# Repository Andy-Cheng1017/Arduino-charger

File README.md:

# Arduino-charger
 Atmega328pau+TypeC+li-on Charger boost PCB

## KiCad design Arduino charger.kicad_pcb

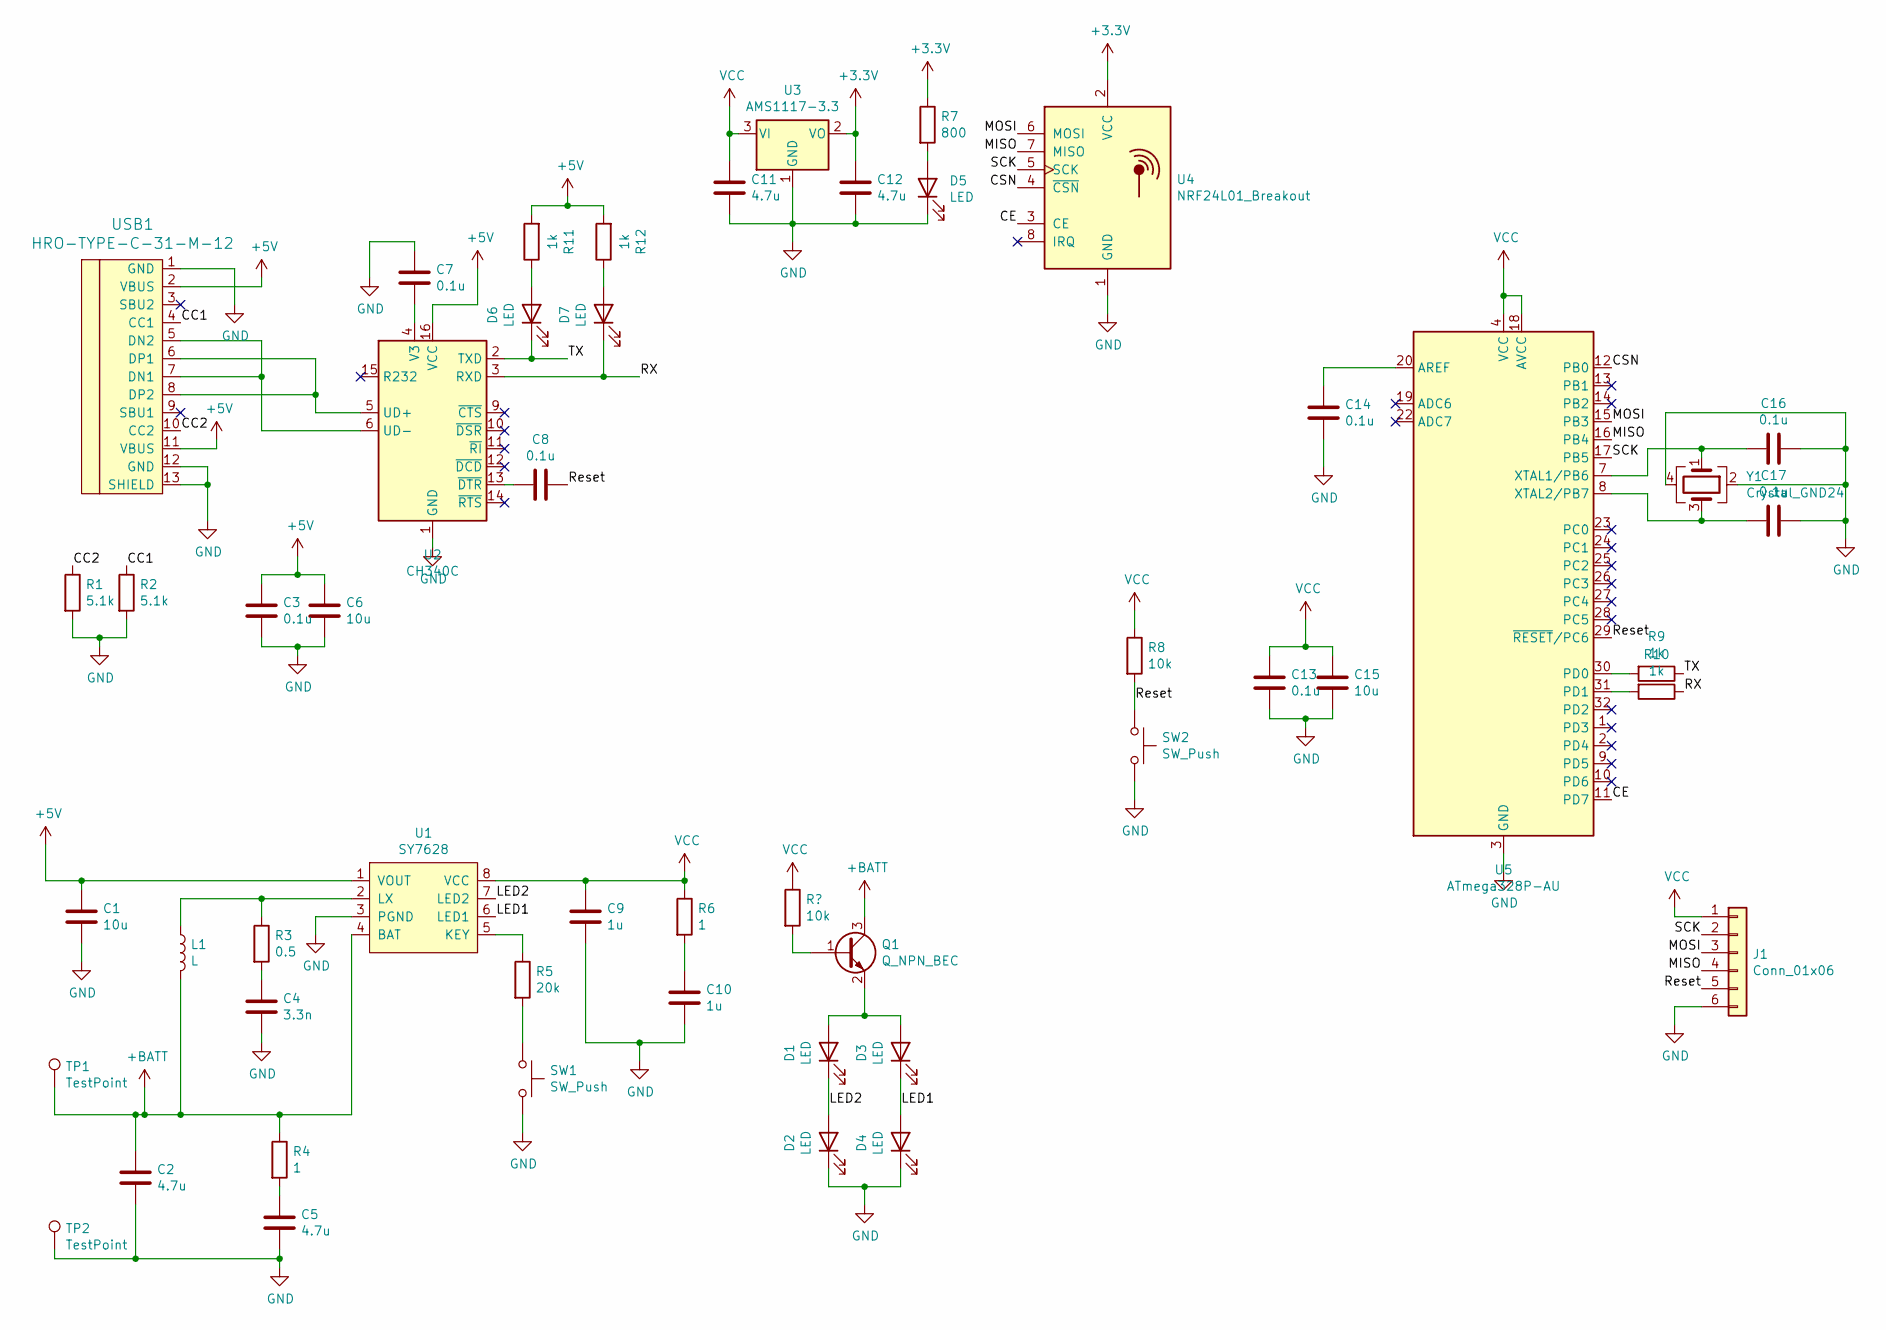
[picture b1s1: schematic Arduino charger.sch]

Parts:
C1, C6, C15: 10u; C_1206_3216Metric
C2, C5, C11, C12: 4.7u; C_0805_2012Metric
C3, C7, C8, C13, C14, C16, C17: 0.1u; C_0805_2012Metric
C4: 3.3n; C_0805_2012Metric
C9, C10: 1u; C_0805_2012Metric
D1, D2, D3, D4, D5, D6, D7: LED; LED_0805_2012Metric
J1: Conn_01x06; PinHeader_1x06_P2.54mm_Vertical
L1: L; L_Bourns-SRN4018
Q1: Q_NPN_BEC; SOT-23
R1, R2: 5.1k; R_0805_2012Metric
R3: 0.5; R_0805_2012Metric
R4, R6: 1; R_0805_2012Metric
R5: 20k; R_0805_2012Metric
R7: 800; R_0805_2012Metric
R8: 10k; R_0805_2012Metric
R9, R10, R11, R12: 1k; R_0805_2012Metric
SW1, SW2: SW_Push; SW_SPST_CK_RS282G05A3
TP1, TP2: TestPoint; TestPoint_Pad_D2.5mm
U1: SY7628; SOIC-8_3.9x4.9mm_P1.27mm
U2: CH340C; SOIC-16_3.9x9.9mm_P1.27mm
U3: AMS1117-3.3; SOT-223-3_TabPin2
U4: NRF24L01_Breakout; NRF24L01-SMD
U5: ATmega328P-AU; TQFP-32_7x7mm_P0.8mm
USB1: HRO-TYPE-C-31-M-12
Y1: Crystal_GND24; Crystal_SMD_3225-4Pin_3.2x2.5mm

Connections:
+3V3: C12.2, R7.1, U3.2 (VO), U4.2 (VCC)
+5V: C1.1, C3.1, C6.1, R11.2, R12.2, U1.1 (VOUT), U2.16 (VCC), USB1.2 (VBUS), USB1.11 (VBUS)
+BATT: C2.2, L1.2, Q1.3 (C), R4.1, TP1.1, U1.4 (BAT)
/CC1: R2.1, USB1.4 (CC1)
/CC2: R1.1, USB1.10 (CC2)
/CE: U4.3 (CE), U5.11 (PD7)
/CSN: U4.4 (~CSN), U5.12 (PB0)
/LED1: D3.1 (K), D4.2 (A), U1.6 (LED1)
/LED2: D1.1 (K), D2.2 (A), U1.7 (LED2)
/MISO: J1.4, U4.7 (MISO), U5.16 (PB4)
/MOSI: J1.3, U4.6 (MOSI), U5.15 (PB3)
/RX: D7.1 (K), R10.1, U2.3 (RXD)
/Reset: C8.1, J1.5, R8.2, SW2.1, U5.29 (~RESET~/PC6)
/SCK: J1.2, U4.5 (SCK), U5.17 (PB5)
/TX: D6.1 (K), R9.1, U2.2 (TXD)
GND: C1.2, C2.1, C3.2, C4.1, C5.1, C6.2, C7.1, C9.1, C10.1, C11.1, C12.1, C13.2, C14.1, C15.2, C16.2, C17.2, D2.1 (K), D4.1 (K), D5.1 (K), J1.6, R1.2, R2.2, SW1.2, SW2.2, TP2.1, U1.3 (PGND), U2.1 (GND), U3.1 (GND), U4.1 (GND), U5.3 (GND), U5.5 (GND), U5.21 (GND), USB1.1 (GND), USB1.12 (GND), USB1.13 (SHIELD), Y1.2, Y1.4
unnamed: C4.2, R3.2
unnamed: C5.2, R4.2
unnamed: C7.2, U2.4 (V3)
unnamed: C8.2, U2.13 (~DTR)
unnamed: C10.2, R6.2
unnamed: C14.2, U5.20 (AREF)
unnamed: C16.1, U5.7 (XTAL1/PB6), Y1.1
unnamed: C17.1, U5.8 (XTAL2/PB7), Y1.3
unnamed: D1.2 (A), D3.2 (A), Q1.2 (E)
unnamed: D5.2 (A), R7.2
unnamed: D6.2 (A), R11.1
unnamed: D7.2 (A), R12.1
unnamed: L1.1, R3.1, U1.2 (LX)
unnamed 29: Q1.1 (B); also elsewhere on the board
unnamed: R5.1, U1.5 (KEY)
unnamed: R5.2, SW1.1
unnamed: R9.2, U5.30 (PD0)
unnamed: R10.2, U5.31 (PD1)
unnamed: U2.5 (UD+), USB1.6 (DP1), USB1.8 (DP2)
unnamed: U2.6 (UD-), USB1.5 (DN2), USB1.7 (DN1)
VCC: C9.2, C11.2, C13.1, C15.1, J1.1, R6.1, R8.1, U1.8 (VCC), U3.3 (VI), U5.4 (VCC), U5.6 (VCC), U5.18 (AVCC); also elsewhere on the board

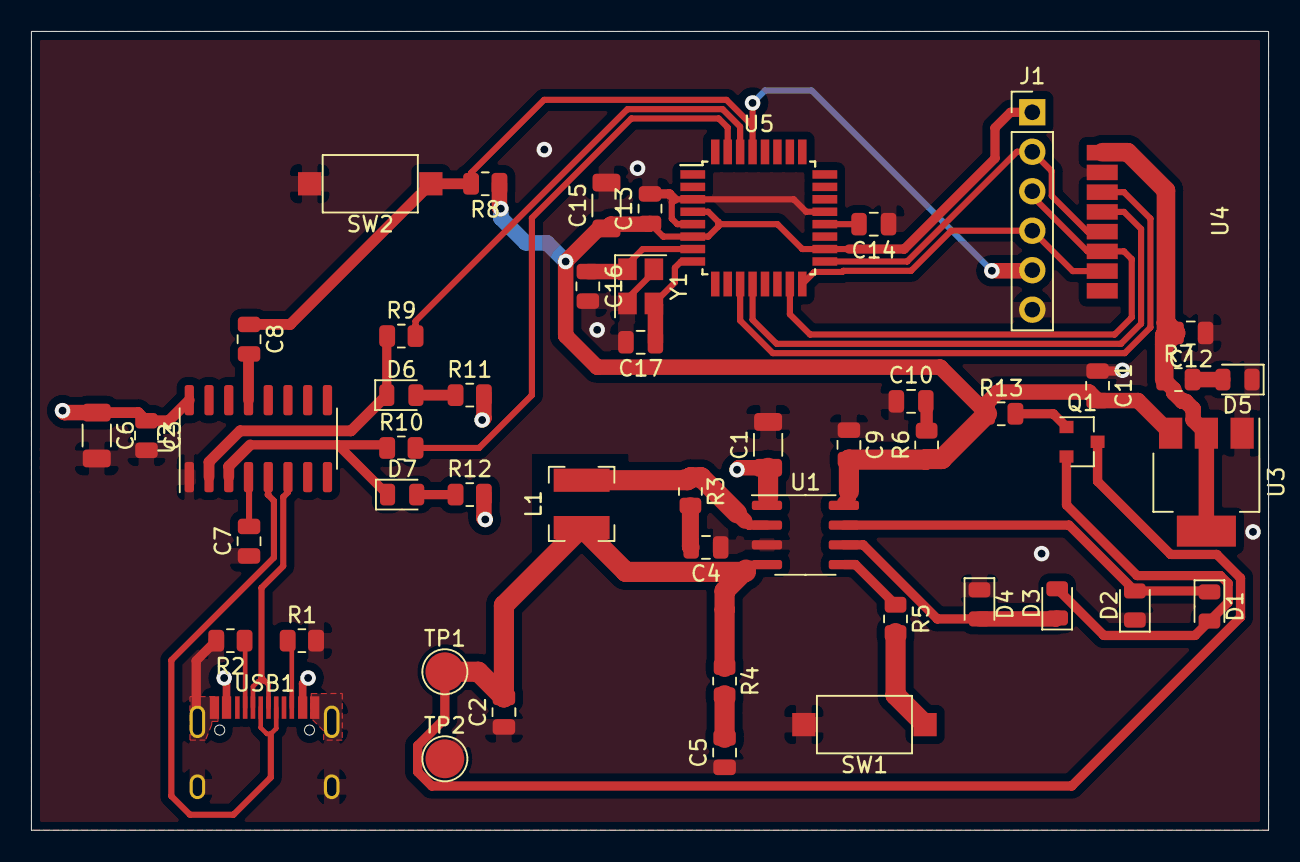
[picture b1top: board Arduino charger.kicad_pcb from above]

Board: 2 copper layers, 79.6 x 51.4 mm, 51 parts (0 on the bottom side), 37 nets.

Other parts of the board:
R13: 10k; R_0805_2012Metric

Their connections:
unnamed 29: R13.2; also elsewhere on the board
VCC: R13.1; also elsewhere on the board

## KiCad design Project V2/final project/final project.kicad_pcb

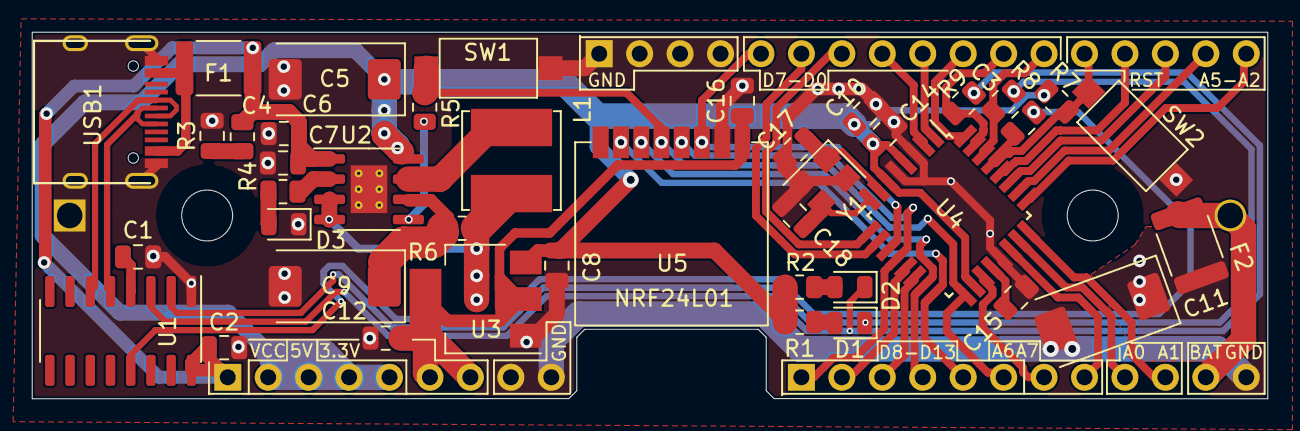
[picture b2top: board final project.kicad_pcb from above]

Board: 2 copper layers, 77.6 x 23.0 mm, 45 parts (1 on the bottom side), 47 nets.

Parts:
BT1: Battery_Cell; BatteryHolder_MPD_BH-18650-PC2
C1, C3, C14, C15, C16: 0.1u; C_0805_2012Metric
C2, C8, C12: 1u; C_0805_2012Metric
C4, C6, C7, C10: 4.7u; C_0805_2012Metric
C5: 150u; CP_EIA-7343-15_Kemet-W
C9, C11: 22u; CP_EIA-7343-15_Kemet-W
C17, C18: 22p; C_0805_2012Metric
D1, D2, D3: LED; LED_0805_2012Metric
F1, F2: Fuse; Fuse_1812_4532Metric
J1: Conn_01x09; PinHeader_1x09_P2.54mm_Vertical
J2: Conn_01x12; PinHeader_1x12_P2.54mm_Vertical
J3: Conn_01x17; PinHeader_1x17_P2.54mm_Vertical
L1: L_Small; L_Bourns_SRN6045TA
R1, R2, R8, R9: 1k; R_0805_2012Metric
R3: 2; R_0805_2012Metric
R4: 200; R_0805_2012Metric
R5, R7: 10k; R_0805_2012Metric
R6: 0.5; R_0805_2012Metric
SW1, SW2: SW_Push; SW_SPST_CK_RS282G05A3
U1: CH340C; SOIC-16_3.9x9.9mm_P1.27mm
U2: IP5306; SOIC-8-1EP_3.9x4.9mm_P1.27mm_EP2.29x3mm_ThermalVias
U3: AMS1117; SOT-223-3_TabPin2
U4: ATmega328P-A; TQFP-32_7x7mm_P0.8mm
U5: NRF24L01_Breakout; NRF24L01-SMD
USB1: HRO-TYPE-C-31-M-12
Y1: Crystal_GND24; Crystal_SMD_3225-4Pin_3.2x2.5mm

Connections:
+3V3: C12.2, C16.2, J1.6, J1.7, U3.2, U5.2
+3V8: C11.1, F2.1, L1.2, R6.2, U2.3, U2.4
+5V: C5.1, C8.2, C10.2, C14.2, J1.2, J1.3, J1.4, J1.5, R1.2, R2.2, R7.2, U2.8, U3.3, U4.4, U4.6, U4.18
+BATT: BT1.1, F2.2, J2.11
/A0: J2.9, U4.23
/A1: J2.10, U4.24
/A2: J3.17, U4.25
/A3: J3.16, U4.26
/A4: J3.15, U4.27
/A5: J3.14, U4.28
/A6: J2.7, U4.19
/A7: J2.8, U4.22
/D0: J3.12, R8.2, U4.30
/D1: J3.11, R9.2, U4.31
/D2: J3.10, U4.32
/D3: J3.9, U4.1
/D4: J3.8, U4.2
/D5: J3.7, U4.9
/D6: J3.6, U4.10
/D7: J3.5, U4.11, U5.3
/D8: J2.1, U4.12, U5.4
/D9: J2.2, U4.13
/D10: J2.3, U4.14
/D11: J2.4, U4.15, U5.6
/D12: J2.5, U4.16, U5.7
/D13: J2.6, R5.1, SW1.1, U4.17, U5.5
/RX: D1.1, R8.1, U1.2
/Reset: C3.1, J3.13, R7.1, SW2.1, U4.29
/TX: D2.1, R9.1, U1.3
GNDA: BT1.2, C1.2, C2.1, C4.1, C5.2, C6.1, C7.1, C8.1, C9.2, C10.1, C11.2, C12.1, C14.1, C15.1, C16.1, C17.1, C18.1, D3.1, J1.8, J1.9, J2.12, J3.1, J3.2, J3.3, J3.4, SW1.2, SW2.2, U1.1, U2.9, U3.1, U4.3, U4.5, U4.21, U5.1, USB1.1, USB1.12, USB1.13, Y1.2, Y1.4
unnamed: C1.1, U1.4
unnamed: C3.2, U1.13
unnamed: C4.2, R3.1
unnamed: C9.1, R6.1, U2.6
unnamed: C15.2, U4.20
unnamed: C17.2, U4.7, Y1.1
unnamed: C18.2, U4.8, Y1.3
unnamed: D1.2, R1.1
unnamed: D2.2, R2.1
unnamed: D3.2, R4.1
unnamed: L1.1, U2.7
unnamed: R4.2, U2.2
unnamed: R5.2, U2.5
unnamed: U1.5, USB1.6, USB1.8
unnamed: U1.6, USB1.5, USB1.7
VBUS: F1.2, USB1.2, USB1.11
VCC: C2.2, C6.2, C7.2, F1.1, J1.1, R3.2, U1.16, U2.1

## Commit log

2021-08-15 upload
    upload
2021-08-18 8/18 update
    gerber送廠
